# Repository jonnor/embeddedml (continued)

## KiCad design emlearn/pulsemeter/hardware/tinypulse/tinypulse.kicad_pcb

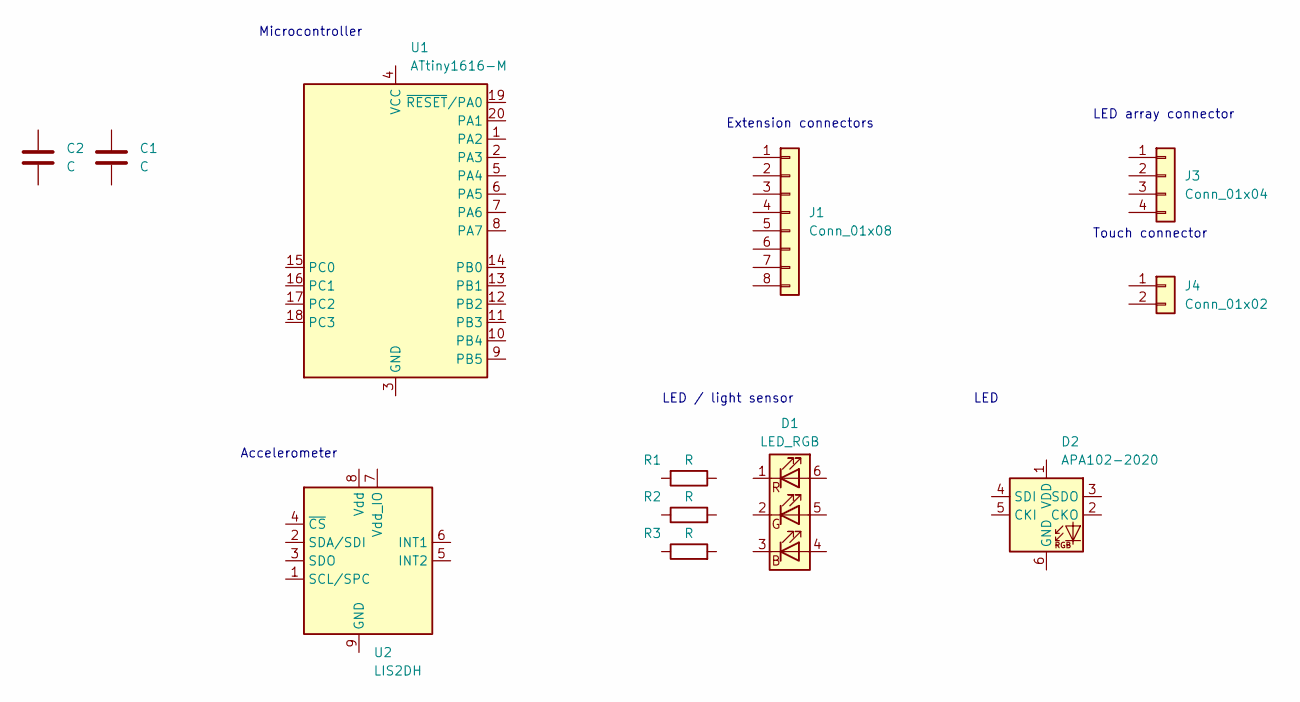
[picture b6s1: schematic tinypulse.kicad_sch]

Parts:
C1, C2: C; C_0603_1608Metric_Pad1.08x0.95mm_HandSolder
D1: LED_RGB; LED_Avago_PLCC6_3x2.8mm
D2: APA102-2020; LED-APA102-2020
J1: Conn_01x08; DIP-8_W10.16mm
J3: Conn_01x04; PinHeader_1x04_P1.27mm_Horizontal
J4: Conn_01x02; PinHeader_1x04_P1.27mm_Horizontal
R1, R2, R3: R; R_0603_1608Metric
U1: ATtiny1616-M; VQFN-20-1EP_3x3mm_P0.4mm_EP1.7x1.7mm
U2: LIS2DH; LGA-14_2x2mm_P0.35mm_LayoutBorder3x4y

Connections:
unnamed: U1.3 (GND), U1.21 (GND)
unnamed: U2.9 (GND), U2.10 (GND), U2.11 (GND), U2.12 (GND), U2.13 (GND), U2.14 (GND)

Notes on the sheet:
LED array connector
LED / light sensor
LED
Accelerometer
Extension connectors
Touch connector
Microcontroller

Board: 2 copper layers, 12 parts (0 on the bottom side), 2 nets, no tracks yet.

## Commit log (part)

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2024-10-01 PyConZA: More notes
2024-10-01 nosienode: Use emliir filter and @native the conversions
    Takes around 130 ms now
2024-10-03 PyConZA: Add slides
2024-10-05 EmbeddedOnlineConference2024: Add slides and video link
2024-10-05 PyDataBerlin2024: Add link to video recording
2024-10-05 TinyMLEMEA2024: Try fix links
2024-10-07 noisenode: Use emlearn_arrayutils.linear_map to convert samples
    Is now able to run in real-time with
    time-integration and frequency weighting on ESP32
2024-10-13 noisenode: Moved soundlevel code to emlearn-micropython
    https://github.com/emlearn/emlearn-micropython/tree/master/examples/soundlevel_iir
2024-10-16 PyDataGlobal2024: Finish basic outline
2024-10-16 emlearn: Update roadmap
2024-10-30 dtmf: Some code for generating the tones
2024-11-11 dollar_tinyml: Misc updates
2024-11-13 FOSDEM2025: Submitted all proposals
2024-11-19 hands-on: Experiment with Quant intervals on Sonar dataset
2024-12-03 PyDataGlobal2024: Skeleton README file
2024-12-04 PyDataGlobal2024: Actually read temperature from MPU6886
2024-12-04 PyDataGlobal2024: Add slides
2024-12-05 dollarml: Some updates
2024-12-15 dollarml: Start next revision
2024-12-15 dollarml: All components placed?
2024-12-15 dollarml: Update references
2024-12-15 dollarml: Layout of rev2 for motion done
2024-12-15 dollarml: Update worklog
2024-12-19 toothbrush: Sketch for application logic
2024-12-20 toothbrush: Happy case passes
2024-12-20 toothbrush: Update notes
2024-12-20 toothbrush: Find a success sound
2024-12-20 toothbrush: Overall business logic tested on device
2024-12-21 toothbrush: Revision 2 of handle
    Has attachment mechanism for brush, using zipties
    Missing a cover
2024-12-26 micropython-ble: Fixup advertising example
2024-12-27 toothbrush: Start exploring existing dataset
2024-12-28 toothbrush: Code for subtracting gravity
2024-12-29 toothbrush: Check frequency spectrum
2024-12-29 toothbrush: Most of labeling prep is ready
2024-12-29 toothbrush: Load labels
2024-12-29 toothbrush: Export labeled dataset to har_trees
2024-12-30 toothbrush: Move processing out of main
2024-12-31 toothbrush: Start analyzing own dataset
2024-12-31 toothbrush: Initial custom data
    Labels need to be aligned with sensor data
2025-01-01 toothbrush: Basic dataset merging in place
    Missing: Proper alignment in time
2025-01-01 toothbrush: Align the labels
2025-01-02 toothbrush: Update 3d model
2025-01-02 toothbrush: Output application state to CSV, set saner max idle time
2025-01-02 toothbrush: Update to model trained on 50 samples window
2025-01-03 toothbrush: Initial code for generating video with overlay
2025-01-03 toothbrush: Try shift timing
    Still not quite right. Need to figure out what actual problem is
2025-01-05 dollarml: Split I2C to BLE, add buzzer
2025-01-05 dml20m: Fix DRC errors
2025-01-05 dollarml: dml20m revision ready for production
2025-01-10 Test a HX711 weightcell amplifier
2025-01-15 hwtrees: Notes on concept and skeleton C code
2025-01-23 FOSDEM2025: Split notes for different talks
2025-01-24 dollarml: Try make PCB longer and flat
2025-01-26 FOSDEM2025: Some presentation notes
2025-02-01 FOSDEM2025: Update notes
2025-02-09 hwtrees: Some updates on system design and notes
2025-02-16 hwtrees: Add some notes
2025-02-25 hwtrees: Some notes on feature extraction
2025-03-08 EmbeddedWorld2025: More notes
2025-03-13 EmbeddedWorld: Upload presentation
2025-03-13 FOSDEM2025: Upload slides
2025-03-27 Aarhus: Add some experiment
2025-03-28 Organize notes
2025-04-08 Add some presentation proposals
2025-04-13 timeseries-compression: Playing with Simple9
    For soundlevel data, or accelerometer values
    int16 native
2025-04-13 foss-north-2025: Initial README
2025-04-13 foss-north-2025: Initial slides
2025-04-15 qemu-peripheral-gdb: Move to folder for GDB approach
2025-04-19 spectroscopy: More notes
2025-04-22 ShowNTell: Add initial notes
2025-04-24 ShowAndTell: Add slides, move to presentation subfolder
2025-04-27 dml20m: Fix bringup worklog
    Was not for dml21m :)
2025-05-08 presentations: Misc updates
2025-05-16 spectroscopy: Add some notes on linear CCD array
2025-06-01 TinyMLDays: Start notes
2025-06-09 TinyMLDays: Some notes on workshop
2025-06-11 TinyMlDays: Notes on perf from DAGHAR dataset compilation paper
2025-06-16 TinyMLDays: Add some notes
2025-07-04 logreg: Claude v1
    Gives inf loss in second iteration
2025-07-04 Claude v2
2025-07-04 logreg: Add Python wrapper and module code
2025-07-04 linreg: Claude try 2
2025-07-04 linreg: Try ARIMAX
2025-07-04 linreg: Data loading
2025-07-05 linreg: Wrapper code from Claude
2025-07-05 linreg: LLM said it fixes things, but it seems worse
2025-07-05 linreg: Avoid dynamic allocation
2025-07-05 linreg: Prameters should go in constructor
2025-07-05 linreg: Seems to basically work for ARIMAX on HVAC dataset
2025-07-05 linreg: HalfNormal works better for anomaly scaling
2025-07-05 linreg: Support penalizing AR/MA terms, to focus on covariates
2025-07-05 linreg: Try get predict of ARIMAX to actually do the work
2025-07-06 spectroscopy: Some notes
2025-07-07 extratrees: Initial sketch
2025-07-07 extratrees: XOR fixed
2025-07-07 extratrees: Vibing, now fails on spiral dataset...
2025-07-07 extratrees: Proper float ratios
2025-07-07 extratrees: Eliminate temp_indices array
    2x RAM savings
2025-07-10 luxmeter: Can read data from AS7343
2025-07-11 luxmeter: Add basic mounting for M5StickC
2025-07-11 luxmeter: Code for reading encoder
2025-07-12 luxmeter: Code for photopic function
2025-07-12 luxmeter: Add a 4th series of measurements
2025-07-12 luxmeter: Move host code into subdirectory
2025-07-12 luxmeter: Also plot raw samples wrt lux
    Shows a huge spread, different near-linear patterns
2025-07-12 luxmeter: Add data for RGB at 100%, different hues
2025-07-12 luxmeter: Another RGB series, at 33% power
2025-07-12 luxmeter: Update model
2025-07-12 luxmeter: Plot sparsity
    Best perfomance with just 1 feature. Suspicious!
2025-07-12 luxmeter: Using a single sample works much better
    RMSE dropped from 80 to 20
    Something funky is going on
2025-07-13 luxmeter: Do grouped splits
2025-07-13 luxmeter: Fix reading of .npy files with bad shape data
2025-07-13 luxmeter: Cleanup training plots
2025-07-13 luxmeter: Try out model on files
    Seems to work!? Predictions within +-20 lux, which is expected
2025-07-13 luxmeter: Add code for running continously
2025-07-16 Notes on TinyTapeout RISC-V
2025-07-20 luxmeter: Scale by specified sensitivities
    Also try out baseline models, and clean some outliers
2025-07-21 luxmeter: Cleanup training loop, separate out files
2025-07-21 Move model export to .py module
2025-07-21 luxmeter: Plot prettification
2025-08-01 micropython-sort: Try quicksort
    Iterative similar to heapsort, but needs extra space
    Recursive is 2x slower than heapsort
2025-08-03 euroscipy2025: Add notes
2025-08-03 OpenSourceSummitEurope: Minor notes
2025-08-09 spectroscopy: Some notes on olive oil quality
2025-08-10 spectrometer: Screen also works
2025-08-10 spectrometer: Fix spacing on AS7343 module
2025-08-18 euroscipy2025: Update notes
2025-08-20 spectrometer: Add rotary encoder module
2025-08-20 spectrometer: Integrate display, encoder, readout
2025-08-23 euroscipy2025: Add some code from sprint
2025-08-23 OSSummit: Update talk notes
2025-08-24 EmbeddedWorld2025: Update notes on Zephyr sensor readout
2025-08-27 OSSummit: Add slides
2025-08-31 AiDev2025: Add slides
2025-09-21 Update some notes
2025-09-24 Update README a bit
2025-10-05 fpga: Some notes
2025-10-05 spectrometer: Store data using npyfile
2025-10-05 spectrometer: Explore the data
    Very good separation for oil in UV, using 2 features
2025-10-05 spectrogram: Support drawing datapoint in X/Y
2025-10-05 spectrometer: Fixup classifier
2025-10-05 spectrometer: Add some data
2025-10-08 micropython: Log the ADC
2025-11-05 spectrometer: Move to https://github.com/jonnor/spectrometer
2025-11-05 Elektor: Update notes
2025-11-11 dollarml: Sketch a post update
2025-11-16 emlearn: Some notes on potential motion subproject
2025-11-20 emlearn: Some musings
2025-11-30 robotics: Some notes
2025-12-14 bbuzz: More notes
2025-12-16 micropython: Add MQTT example
2025-12-20 OSHW2026: Proposal ready?
2025-12-21 bbuzz: Is in 2026
2025-12-21 PyConDE2026: Split proposal out from notes
2025-12-21 emlearn: Misc notes
2025-12-27 rowing-counter: Initial code skeleton for recording
2025-12-27 rowing-counter: Move firmware to own folder
2025-12-28 rowing-counter: Indicate startup and record on LEDs
2025-12-28 rowing-counter: Initial analysis algorithm
2026-01-01 Add notes on differentiable programming
2026-01-25 hwtrees: Add some notes on CGRAs
2026-01-31 fpga-riscv: Some notes on LiteX
2026-02-01 Revert "fpga-riscv: Try the xenador77 fork for upduino"
    This reverts commit f850e0809419aadceee4f24cc9cabd1a901a2b02.
2026-02-01 fpga-riscv: Got LiteX working on ICESugar
2026-02-01 fpga-riscv: Try customize target to add GPIO
2026-02-03 fpga-riscv: Automatically rebuild firmware if specified
    Fix linker error on serv etc due to missing libgcc
    Also add in crt0 and isr, hope it would fix blinky not working on non- vexrisc CPUS
    It dis not
2026-02-03 fpga-riscv: Use linker and makefile from litex_bare_metal_demo
2026-02-05 fpga-riscv: Try linker.ld from BIOS
2026-02-06 fpga-riscv: Also support running demo program
2026-02-06 fpga-riscv: Try out a custom peripheral, PWM by @riktw
2026-02-06 fpga-riscv: Use a Verilog file in adder module
2026-02-07 fpga-riscv: Remove mention of neorv32
2026-02-07 fpga-riscv: Test of interrupts from Verilog
2026-02-07 fpga-riscv: Add in PDM peripheral
    Seems to be triggering interrupts,
    however program can only handle 1600 ints/second now. Need 10x
    Have not verified PDM clock signal
2026-02-07 fpga-riscv: Try fix interrupt rate
    Current value does not make sense...
    But seem to be able to sustain 16k samplerate
2026-02-07 fpga-riscv: Try fix interrupt rate again
2026-02-07 fpga-riscv: Try RMS computation
2026-02-08 README: Add one more presentation
2026-02-15 EuroPython2026: Proposals submitted
2026-02-18 fpga-riscv: More attempts at Zephyr
2026-02-22 euroscipy2026: Fix wrong path
2026-02-22 fpga-riscv: Bump FLASH size to 1 MB
    Preparing for MicroPython build including filesystem
2026-02-23 fpga-riscv: Still struggling with JTAG on ICE40
2026-03-02 fpga-riscv: Disable PDM/interrupt for now
2026-03-17 differentiable-programming: Add some notes
2026-03-19 PyConDE: Some tests of IMU data compression using PAMAP2 dataset
2026-03-29 Add learning summary for MicroPython ESP32 web server project
2026-03-29 Add MicroPython server and benchmark
2026-03-29 PyConDE: Some test results
2026-03-29 micropython-vibes: Add some notes
2026-04-01 PyConDE: More notes on time-series storage
2026-04-02 PyConDE: Update notes
2026-04-14 PyConDE: Update README with some links
2026-04-15 PyConDE: More notes
2026-04-15 HAR: Add some notes on overall activity
2026-04-22 micropython-vibes: Notes on testing Qwen 3.6
2026-05-09 micropython-vibes: Add systemd service file for llama-cpp-server
2026-05-14 micropython-vibes: Notes on dual GPU plans
2026-05-15 micropython-vibes: Test on new X570 motherboard
2026-05-16 micropython-vibes: First try with 2 gpus
2026-05-18 micropython-vibes: First test for Qwen 3.6 27B with MTP
2026-05-23 micropython-vibes: Initial notes on vLLM
2026-05-24 micropython-vibes: More vLLM and OpenWebUI testing
2026-05-25 presentations: Accepted for EuroScipy and EuroPython 2026
2026-05-25 tutorial: More Wokwi testing, split planning docs
2026-05-26 AarhusUniversity2026: Add presentation
2026-05-26 presentation: Update overview
2026-05-29 micropython-vibes: Updated with newer llama-cpp
2026-05-29 micropython-vibes: Some notes on triple/quad with x570
2026-05-31 micropython-vibes: Notes on testing quad GPU
2026-06-01 micropython-vibes: Concurrency tests on llama-cpp
2026-06-07 miropython-vibes: WIP on eval and Gemma 4
